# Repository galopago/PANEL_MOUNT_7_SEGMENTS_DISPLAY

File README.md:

# PANEL MOUNT 7 SEGMENT SERIALLY CONTROLED LED DISPLAYS

Open source 7 segment serially controlled led display that fits inside a generic 45x26mm panel mount plastic enclosure. Upgrade your function specific panel meter PCB with a new one controllable by your preferred MCU.

Read this in other languages: [Español](/assets/markdown/README.es.md)

Upgrading a 5 digit voltmeter PCB with a 5 digit serially controllable display

0.36 Inch 5 Digits voltmeter                  | 0.36 Inch 5 Digits serially controllable     
----------------------------------------------|----------------------------------------------
            | 
        | 
         | 

The display can be now controlled by Arduino (or any other) boards via serial bus, to display numbers, letters, or individual segments.

## Versions

There are several board versions, each one with different personalities

| HINT                               | CONTROLLER CHIP | LINK                                     
|------------------------------------|-----------------|--------------------------------------
| 056 INCH 3 DIGIT                   | TM1637          | [056 INCH 3 DIGIT](/056-inch-3-digit)  
| 036 INCH 5 DIGIT                   | TM1637          | [036 INCH 5 DIGIT](/036-inch-5-digit)  
| 028 INCH 8 DIGIT (2 Lines x 4Digit)| MAX7219         | [028 INCH 8 DIGIT](/028-inch-8-digit)

0.56 Inch 3 Digits                            | 0.36 Inch 5 Digits                            | 0.28 Inch 8 Digits 
----------------------------------------------|-----------------------------------------------|----------------------------------------------
 |  |

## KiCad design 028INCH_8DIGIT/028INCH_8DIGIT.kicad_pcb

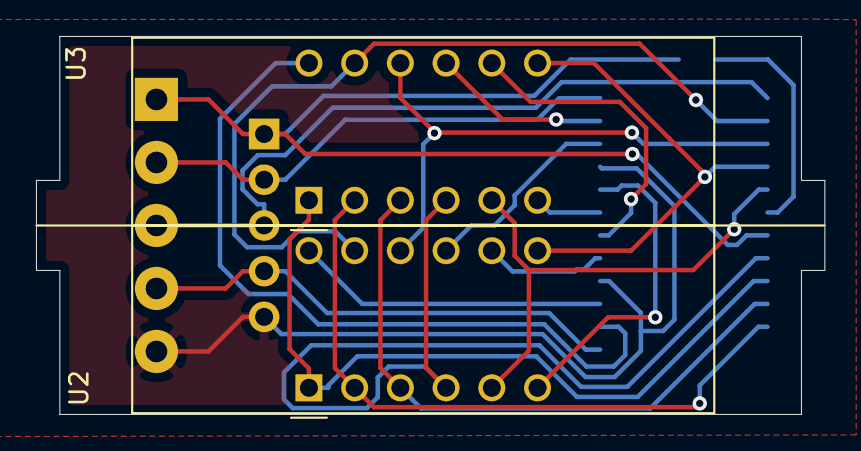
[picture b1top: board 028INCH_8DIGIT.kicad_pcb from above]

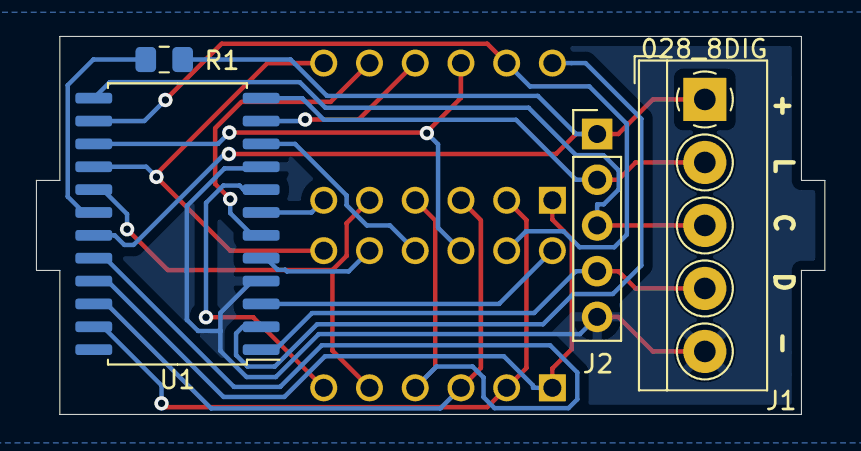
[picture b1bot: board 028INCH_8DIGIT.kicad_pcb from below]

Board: 2 copper layers, 43.8 x 21.0 mm, 6 parts (4 on the bottom side), 22 nets.

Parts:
J1: Conn_01x05_Female; TerminalBlock_4Ucon_1x05_P3.50mm_Horizontal
J2: Conn_01x05_Male; PinHeader_1x05_P2.54mm_Vertical
R1: 10k; R_0805_2012Metric_Pad1.15x1.40mm_HandSolder
U1: MAX7219; SOIC-24W_7.5x15.4mm_P1.27mm
U2, U3: CC56-12CGKWA; 2841AS

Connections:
unnamed: J1.1, J2.1, R1.1, U1.19
unnamed: J1.2, J2.2, U1.12
unnamed: J1.3, J2.3, U1.13
unnamed: J1.4, J2.4, U1.1
unnamed: J1.5, J2.5, U1.4, U1.9
unnamed: R1.2, U1.18
unnamed: U1.2, U3.12
unnamed: U1.3, U2.12
unnamed: U1.5, U2.8
unnamed: U1.6, U3.8
unnamed: U1.7, U3.6
unnamed: U1.8, U2.6
unnamed: U1.10, U2.9
unnamed: U1.11, U3.9
unnamed: U1.14, U2.11, U3.11
unnamed: U1.15, U2.10, U3.10
unnamed: U1.16, U2.7, U3.7
unnamed: U1.17, U2.5, U3.5
unnamed: U1.20, U2.4, U3.4
unnamed: U1.21, U2.1, U3.1
unnamed: U1.22, U2.3, U3.3
unnamed: U1.23, U2.2, U3.2

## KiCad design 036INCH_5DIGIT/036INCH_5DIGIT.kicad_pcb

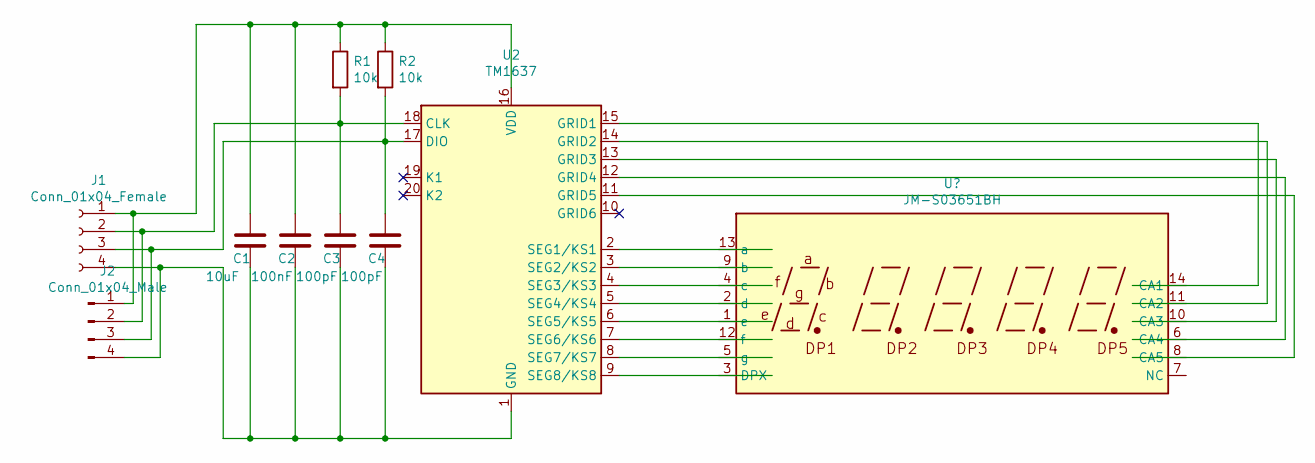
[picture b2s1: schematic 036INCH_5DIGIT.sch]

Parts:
C1: 10uF; C_0805_2012Metric_Pad1.15x1.40mm_HandSolder
C2: 100nF; C_0805_2012Metric_Pad1.15x1.40mm_HandSolder
C3, C4: 100pF; C_0805_2012Metric_Pad1.15x1.40mm_HandSolder
J1: Conn_01x04_Female; TerminalBlock_4Ucon_1x04_P3.50mm_Horizontal
J2: Conn_01x04_Male; PinHeader_1x04_P2.54mm_Vertical
R1, R2: 10k; R_0805_2012Metric_Pad1.15x1.40mm_HandSolder
U2: TM1637; SO-20_12.8x7.5mm_P1.27mm

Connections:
unnamed: C1.1, C2.1, J1.1, J2.1, R1.1, R2.1, U2.16 (VDD)
unnamed: C1.2, C2.2, C3.2, C4.2, J1.4, J2.4, U2.1 (GND)
unnamed: C3.1, J1.2, J2.2, R1.2, U2.18 (CLK)
unnamed: C4.1, J1.3, J2.3, R2.2, U2.17 (DIO)
unnamed 4: U2.6 (SEG5/KS5); also elsewhere on the board
unnamed 5: U2.5 (SEG4/KS4); also elsewhere on the board
unnamed 6: U2.9 (SEG8/KS8); also elsewhere on the board
unnamed 7: U2.4 (SEG3/KS3); also elsewhere on the board
unnamed 8: U2.8 (SEG7/KS7); also elsewhere on the board
unnamed 9: U2.12 (GRID4); also elsewhere on the board
unnamed 11: U2.11 (GRID5); also elsewhere on the board
unnamed 12: U2.3 (SEG2/KS2); also elsewhere on the board
unnamed 13: U2.13 (GRID3); also elsewhere on the board
unnamed 14: U2.14 (GRID2); also elsewhere on the board
unnamed 15: U2.7 (SEG6/KS6); also elsewhere on the board
unnamed 16: U2.2 (SEG1/KS1); also elsewhere on the board
unnamed 17: U2.15 (GRID1); also elsewhere on the board

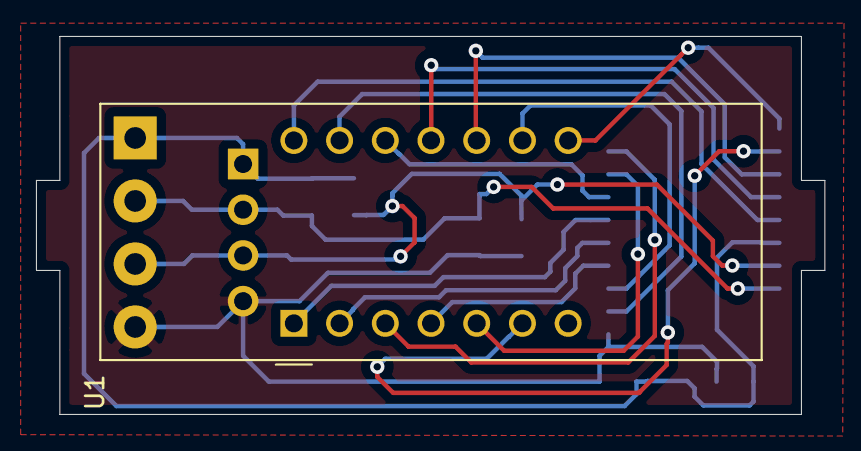
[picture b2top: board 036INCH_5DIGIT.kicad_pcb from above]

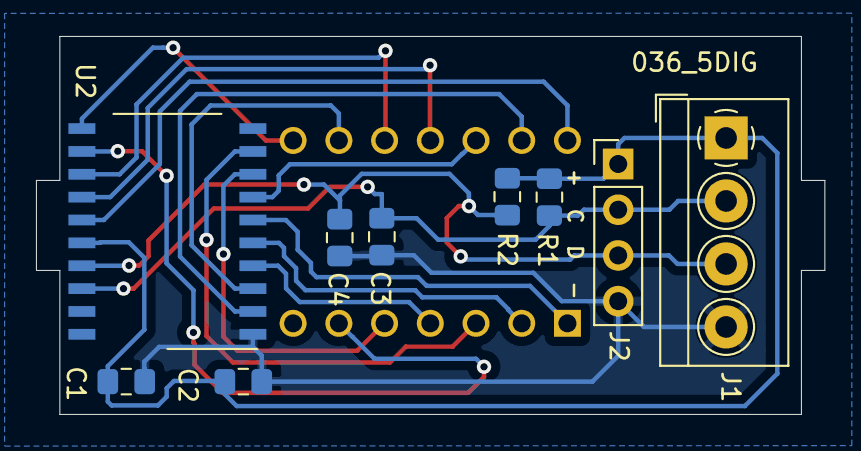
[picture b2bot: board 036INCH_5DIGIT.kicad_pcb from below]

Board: 2 copper layers, 43.8 x 21.0 mm, 10 parts (9 on the bottom side), 17 nets.

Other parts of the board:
U1: JM-S03651BH

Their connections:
unnamed 4: U1.1; also elsewhere on the board
unnamed 5: U1.2; also elsewhere on the board
unnamed 6: U1.3; also elsewhere on the board
unnamed 7: U1.4; also elsewhere on the board
unnamed 8: U1.5; also elsewhere on the board
unnamed 9: U1.6; also elsewhere on the board
unnamed 11: U1.8; also elsewhere on the board
unnamed 12: U1.9; also elsewhere on the board
unnamed 13: U1.10; also elsewhere on the board
unnamed 14: U1.11; also elsewhere on the board
unnamed 15: U1.12; also elsewhere on the board
unnamed 16: U1.13; also elsewhere on the board
unnamed 17: U1.14; also elsewhere on the board

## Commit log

2021-11-11 initial meas
2021-11-11 board outline dimensions finished
2021-11-12 halfway 3 digit display symbol
2021-11-12 3 digit display symbol & footprint finished
2021-11-12 TM1637 symbol finished
2021-11-12 first connections schematic
2021-11-12 all traces routed
2021-11-12 jingmei display symbol started
2021-11-12 jingmei display symbol finished
2021-11-13 jingmei display footprint finished
2021-11-13 starting placing elements in pcb
2021-11-13 4 digit 0.28 inch display footprint finished
2021-11-13 start element placing
2021-11-13 all elements placed
2021-11-16 single board gerber
2021-11-16 panel board gerber
2022-03-13 doc:(panel-mount-7-segments-display ROOT)renamed folders
2022-03-13 doc:(panel-mount-7-segments-display ROOT)renamed folders+
2022-03-14 doc:(panel-mount-7-segments-display ROOT)readme+pics
2022-03-14 doc:(panel-mount-7-segments-display ROOT)readme+pics+
2022-03-14 doc:(panel-mount-7-segments-display ROOT)readme++
2022-03-14 doc:(panel-mount-7-segments-display ROOT)readme+++
2022-03-14 doc:(panel-mount-7-segments-display ROOT)readme++++
2022-03-14 doc:(panel-mount-7-segments-display ROOT)readme+++++
2022-03-14 doc:(panel-mount-7-segments-display ROOT)readme++++++
2022-03-14 doc:(panel-mount-7-segments-display ROOT)readme+++++++
2022-03-14 doc:(panel-mount-7-segments-display ROOT)readme++++++++
2022-03-14 doc:(panel-mount-7-segments-display ROOT)readme+++++++++
2022-03-14 doc:(panel-mount-7-segments-display ROOT)readme+++++++++++
2022-03-14 doc:(panel-mount-7-segments-display ROOT)readme++++++++++++
2022-03-14 doc:(panel-mount-7-segments-display ROOT)readme ES started
2022-03-14 doc:(panel-mount-7-segments-display ROOT)readme ES+
2022-03-14 doc:(panel-mount-7-segments-display ROOT)readme ES++
2022-03-14 doc:(panel-mount-7-segments-display ROOT)readme ES+++
2022-03-14 doc:(panel-mount-7-segments-display ROOT)readme ES++++
2022-03-15 doc:(panel-mount-7-segments-display 056-3-digit)readme started
2022-03-15 doc:(panel-mount-7-segments-display 056-3-digit)readme started+
2022-03-15 doc:(panel-mount-7-segments-display 056-3-digit)readme started++
2022-03-15 doc:(panel-mount-7-segments-display 056-3-digit)readme started+++
2022-03-15 doc:(panel-mount-7-segments-display 056-3-digit)readme started++++
2022-03-15 doc:(panel-mount-7-segments-display 056-3-digit)readme started+++++
2022-03-15 doc:(panel-mount-7-segments-display 056-3-digit)readme started++++++
2022-03-15 doc:(panel-mount-7-segments-display 036-5-digit)readme started
2022-03-15 doc:(panel-mount-7-segments-display 036-5-digit)readme started+
2022-03-15 doc:(panel-mount-7-segments-display 036-5-digit)changed pic
2022-03-15 doc:(panel-mount-7-segments-display 036-3-digit)changed pic+
2022-03-15 doc:(panel-mount-7-segments-display 028-8-digit)started readme
2022-03-15 doc:(panel-mount-7-segments-display root)license
2022-07-14 added table with pics
